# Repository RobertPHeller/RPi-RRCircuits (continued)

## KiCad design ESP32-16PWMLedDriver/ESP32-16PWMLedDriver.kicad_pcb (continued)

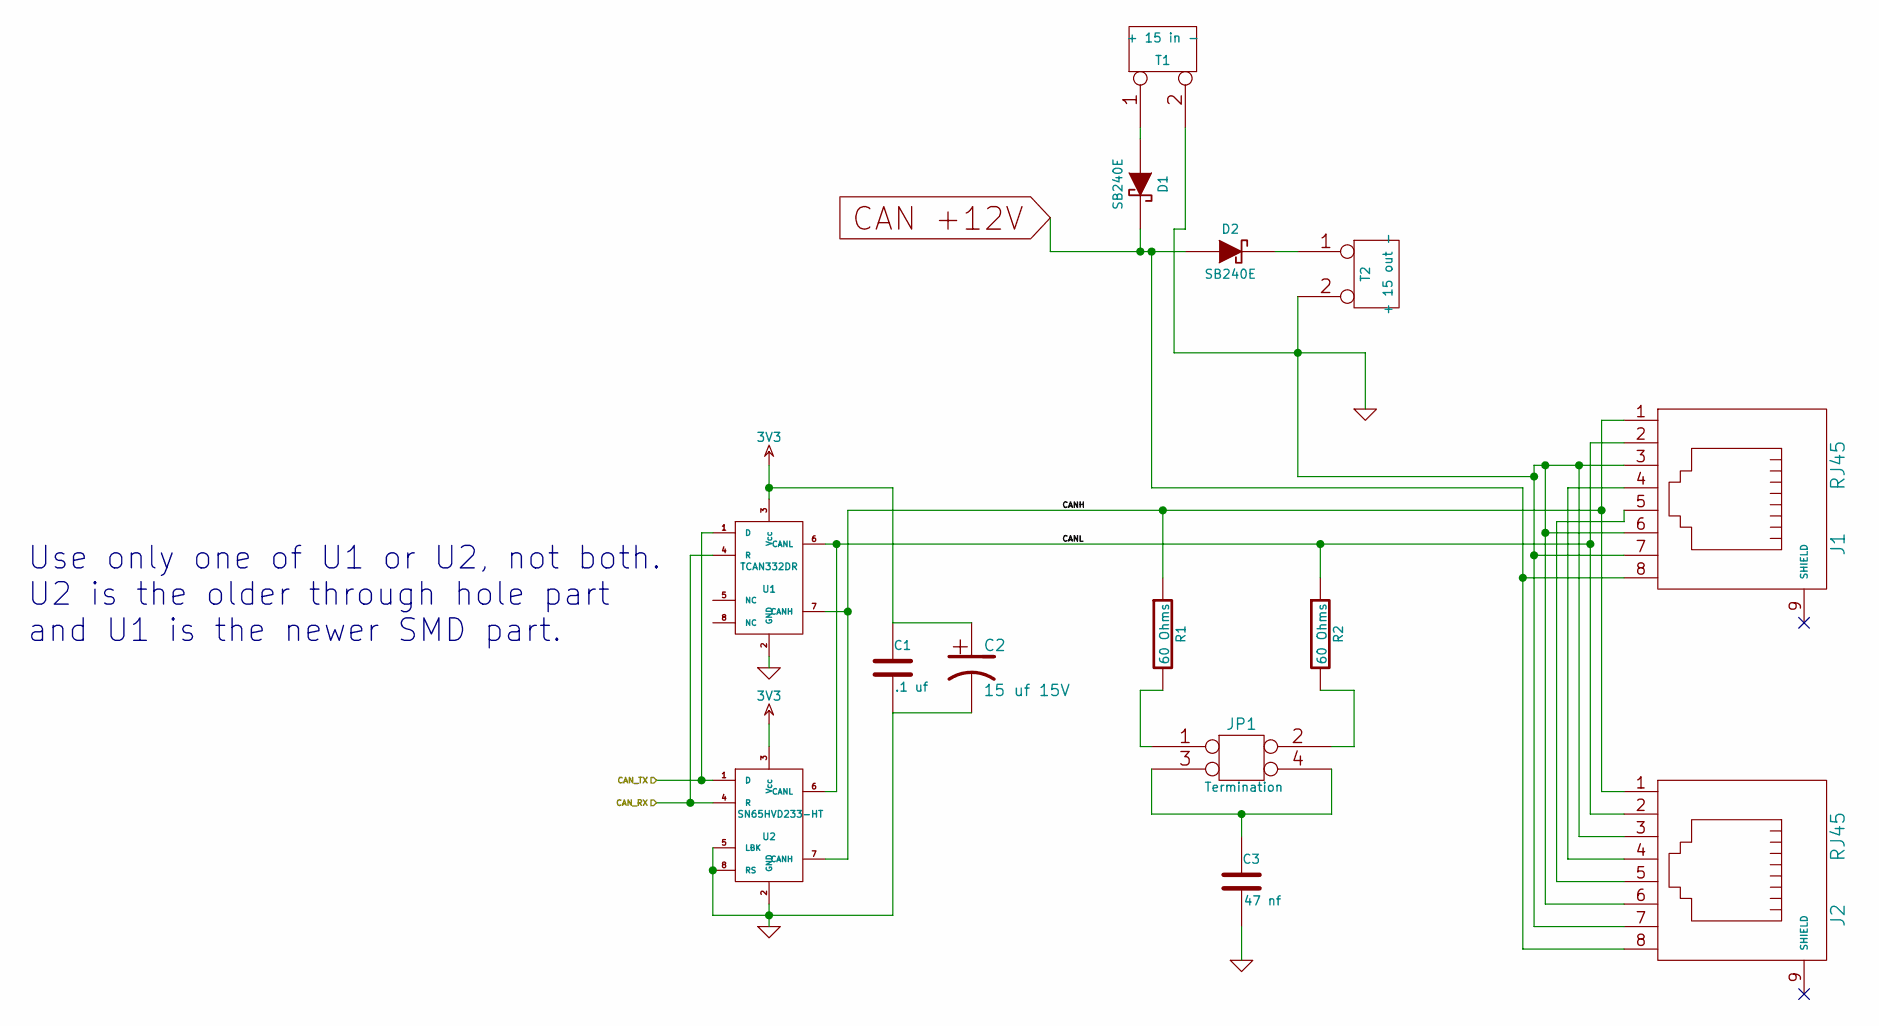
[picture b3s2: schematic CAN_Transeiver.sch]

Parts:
C1: .1 uf
C2: 15 uf 15V
C3: 47 nf
D1, D2: SB240E
J1, J2: RJ45
JP1: Termination
R1, R2: 60 Ohms
T1: + 15 in -
T2: + 15 out -
U1: TCAN332DR
U2: SN65HVD233-HT

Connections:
3V3: C1.1, C2.1, U1.3 (Vcc), U2.3 (Vcc); also elsewhere on the board
/CAN Transceiver/CANH: J1.1, J2.1, R1.1, U1.7 (CANH), U2.7 (CANH)
/CAN Transceiver/CANL: J1.2, J2.2, R2.1, U1.6 (CANL), U2.6 (CANL)
/CAN Transceiver/CAN_RX: U1.4 (R), U2.4 (R); also elsewhere on the board
/CAN Transceiver/CAN_TX: U1.1 (D), U2.1 (D); also elsewhere on the board
CAN +12V: D1.2 (K), D2.1 (A), J1.8, J2.8; also elsewhere on the board
GND: C1.2, C2.2, C3.2, J1.3, J1.6, J1.7, J2.3, J2.6, J2.7, T1.2 (PM), T2.2 (PM), U1.2 (GND), U2.2 (GND), U2.5 (LBK), U2.8 (RS); also elsewhere on the board
unnamed: J1.4, J2.4
unnamed: J1.5, J2.5
unnamed: D1.1 (A), T1.1
unnamed: D2.2 (K), T2.1
unnamed: JP1.2, R2.2
unnamed: C3.1, JP1.3, JP1.4
unnamed: JP1.1, R1.2

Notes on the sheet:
Use only one of U1 or U2, not both. U2 is the older through hole part and U1 is the newer SMD part.

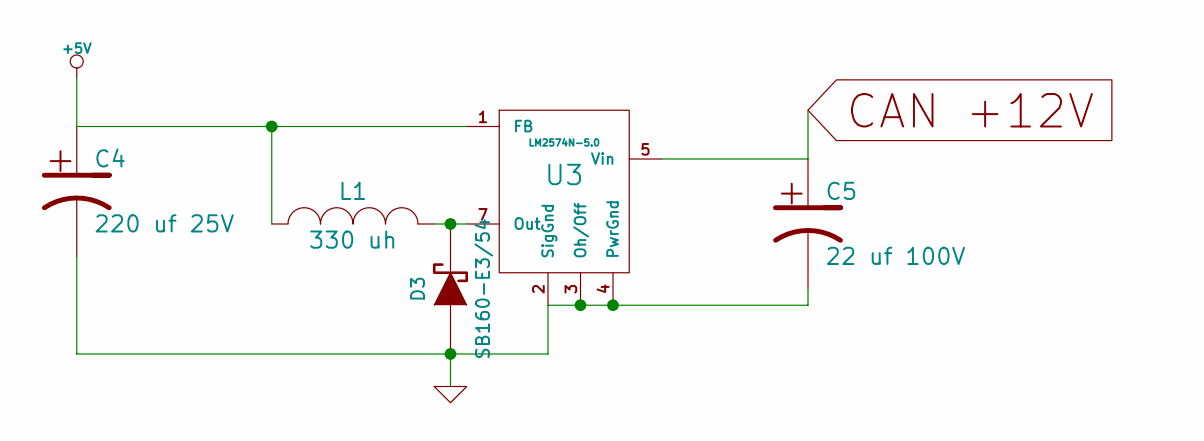
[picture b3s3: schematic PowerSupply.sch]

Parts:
C4: 220 uf 25V
C5: 22 uf 100V
D3: SB160-E3/54
L1: 330 uh
U3: LM2574N-5.0

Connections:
+5V: C4.1, L1.1, U3.1 (FB); also elsewhere on the board
CAN +12V: C5.1, U3.5 (Vin); also elsewhere on the board
GND: C4.2, C5.2, D3.1 (A), U3.2 (SigGnd), U3.3 (Oh/Off), U3.4 (PwrGnd); also elsewhere on the board
unnamed: D3.2 (K), L1.2, U3.7 (Out)

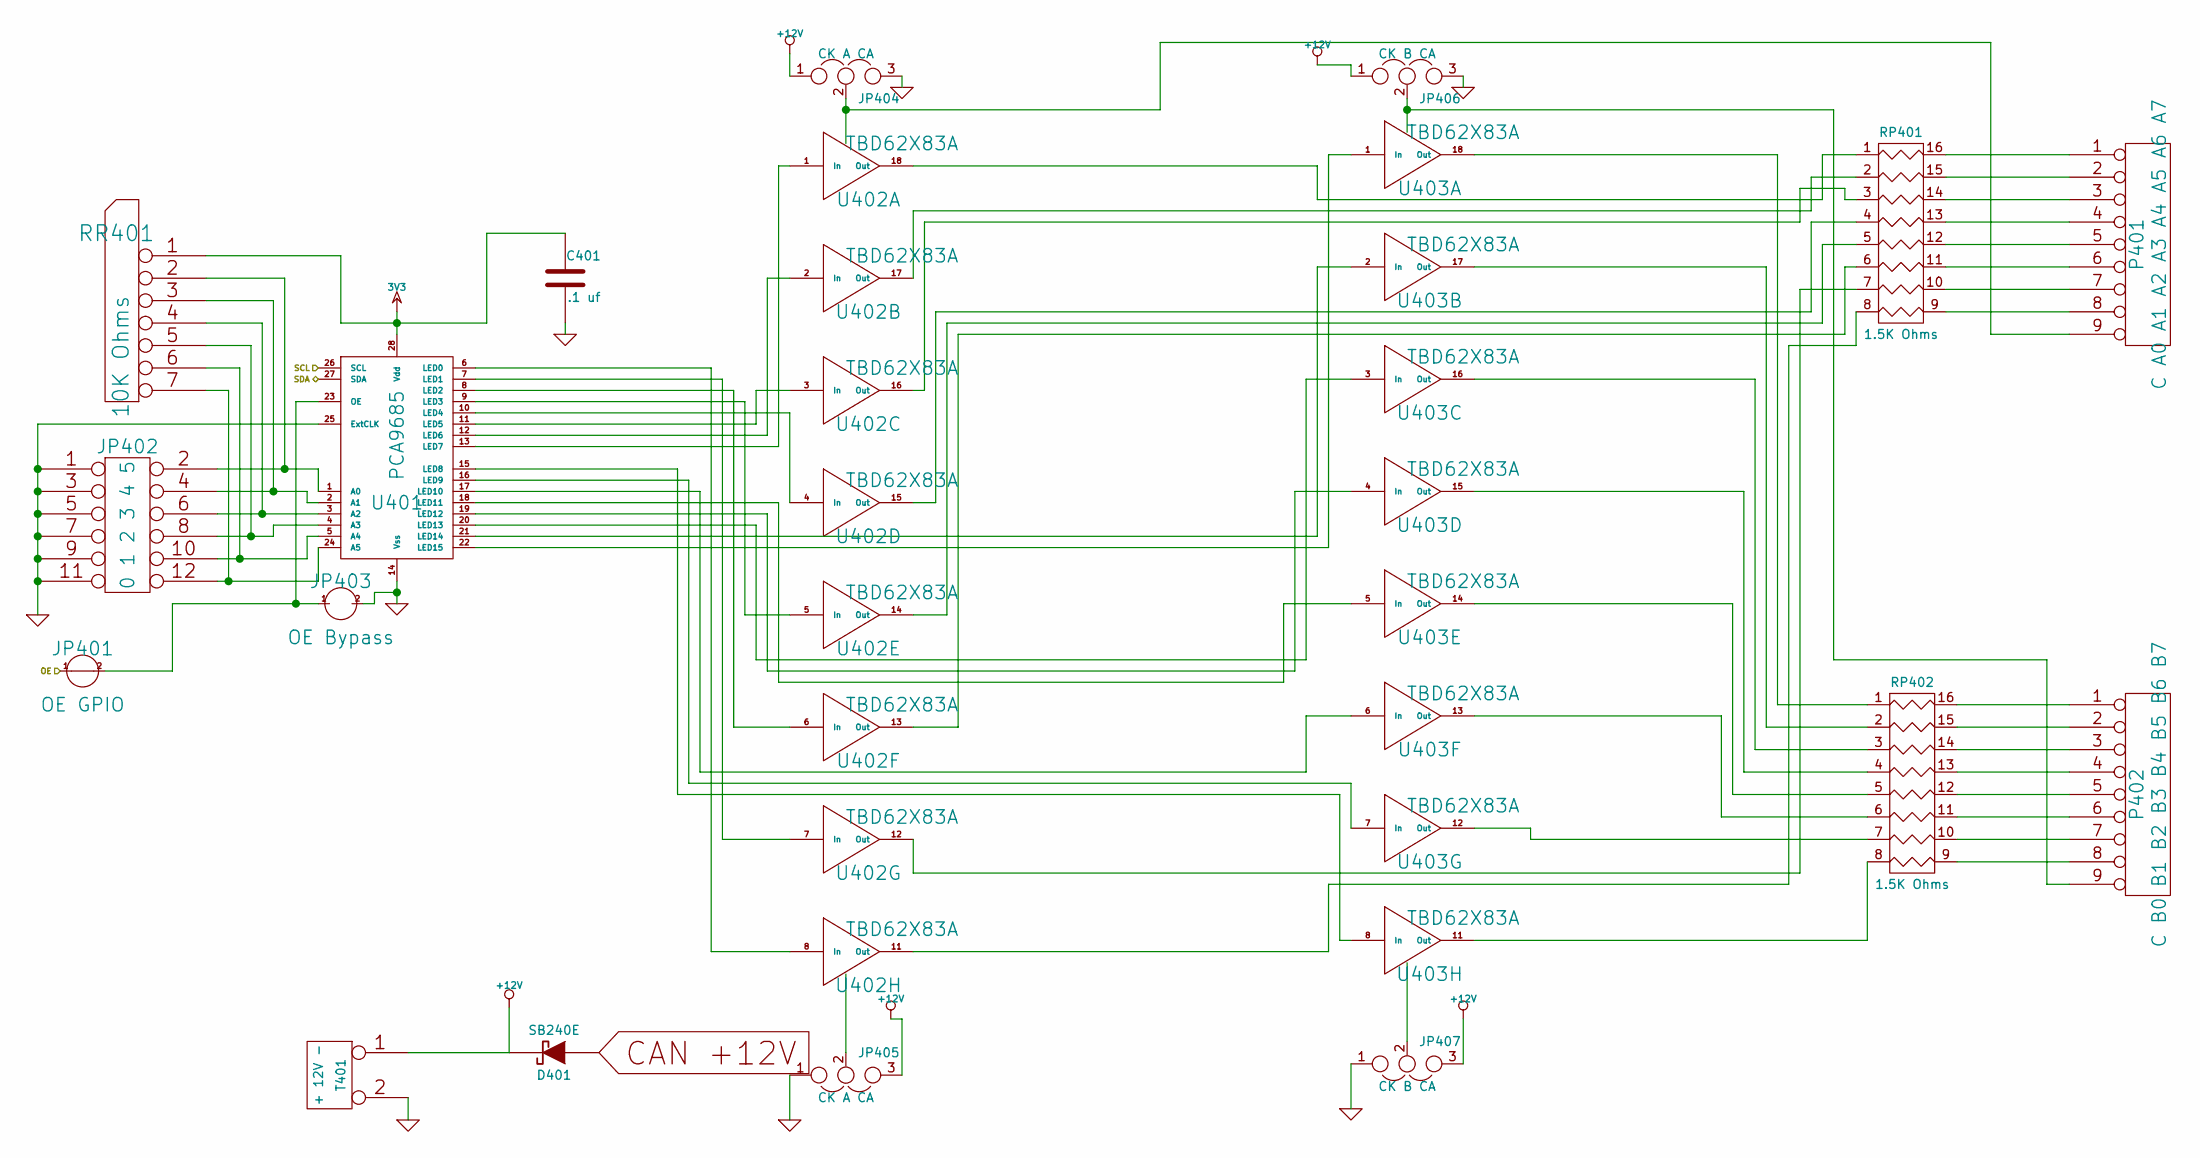
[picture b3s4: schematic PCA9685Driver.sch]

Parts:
C401: .1 uf
D401: SB240E
JP401: OE GPIO
JP402: 0 1 2 3 4 5
JP403: OE Bypass
JP404, JP405: CK A CA
JP406, JP407: CK B CA
P401: C A0 A1 A2 A3 A4 A5 A6 A7
P402: C B0 B1 B2 B3 B4 B5 B6 B7
RP401, RP402: 1.5K Ohms
RR401: 10K Ohms
T401: + 12V -
U401: PCA9685
U402, U403: TBD62X83A

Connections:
3V3: C401.1, RR401.1 (COM), U401.28 (Vdd); also elsewhere on the board
+12V: D401.2 (K), JP404.1, JP405.3, JP406.1, JP407.3, T401.1
/PCA9685 Driver/OE: JP401.1; also elsewhere on the board
/PCA9685 Driver/SCL: U401.26 (SCL); also elsewhere on the board
/PCA9685 Driver/SDA: U401.27 (SDA); also elsewhere on the board
CAN +12V: D401.1 (A); also elsewhere on the board
GND: C401.2, JP402.1, JP402.3, JP402.5, JP402.7, JP402.9, JP402.11, JP403.2, JP404.3, JP405.1, JP406.3, JP407.1, T401.2 (PM), U401.14 (Vss), U401.25 (ExtCLK); also elsewhere on the board
unnamed: P401.4, RP401.13 (R4)
unnamed: P401.5, RP401.12 (R5)
unnamed: P401.6, RP401.11 (R6)
unnamed: P401.7, RP401.10 (R7)
unnamed: P401.8, RP401.9 (R8)
unnamed: P402.1, RP402.16 (R1)
unnamed: P402.2, RP402.15 (R2)
unnamed: P402.3, RP402.14 (R3)
unnamed: P402.4, RP402.13 (R4)
unnamed: P402.5, RP402.12 (R5)
unnamed: P402.6, RP402.11 (R6)
unnamed: P402.7, RP402.10 (R7)
unnamed: P402.8, RP402.9 (R8)
unnamed: P401.3, RP401.14 (R3)
unnamed: P401.2, RP401.15 (R2)
unnamed: P401.1, RP401.16 (R1)
unnamed: JP406.2, P402.9, U403.10 (OC)
unnamed: JP404.2, P401.9, U402.10 (OC)
unnamed: RP401.5, U402.14 (Out)
unnamed: RP401.4, U402.15 (Out)
unnamed: RP401.3, U402.16 (Out)
unnamed: RP401.2, U402.17 (Out)
unnamed: RP401.1, U402.18 (Out)
unnamed: U401.19 (LED12), U403.4 (In)
unnamed: U401.20 (LED13), U403.3 (In)
unnamed: U401.21 (LED14), U403.2 (In)
unnamed: U401.22 (LED15), U403.1 (In)
unnamed: U401.6 (LED0), U402.8 (In)
unnamed: U401.8 (LED2), U402.6 (In)
unnamed: U401.9 (LED3), U402.5 (In)
unnamed: U401.10 (LED4), U402.4 (In)
unnamed: U401.11 (LED5), U402.3 (In)
unnamed: JP405.2, U402.9 (IC)
unnamed: JP407.2, U403.9 (IC)
unnamed: U401.15 (LED8), U403.8 (In)
unnamed: U401.16 (LED9), U403.7 (In)
unnamed: U401.7 (LED1), U402.7 (In)
unnamed: U401.17 (LED10), U403.6 (In)
unnamed: U401.18 (LED11), U403.5 (In)
unnamed: JP402.4, RR401.3, U401.2 (A1)
unnamed: JP402.6, RR401.4, U401.3 (A2)
unnamed: JP402.8, RR401.5, U401.4 (A3)
unnamed: JP402.10, RR401.6, U401.5 (A4)
unnamed: JP401.2, JP403.1, U401.23 (OE)
unnamed: RP402.5, U403.14 (Out)
unnamed: RP402.4, U403.15 (Out)
unnamed: RP402.3, U403.16 (Out)
unnamed: RP402.2, U403.17 (Out)
unnamed: RP402.1, U403.18 (Out)
unnamed: RP401.8, U402.11 (Out)
unnamed: RP401.7, U402.12 (Out)
unnamed: RP401.6, U402.13 (Out)
unnamed: JP402.12, RR401.7, U401.24 (A5)
unnamed: JP402.2, RR401.2, U401.1 (A0)
unnamed: RP402.8, U403.11 (Out)
unnamed: RP402.7, U403.12 (Out)
unnamed: RP402.6, U403.13 (Out)
unnamed: U401.12 (LED6), U402.2 (In)
unnamed: U401.13 (LED7), U402.1 (In)

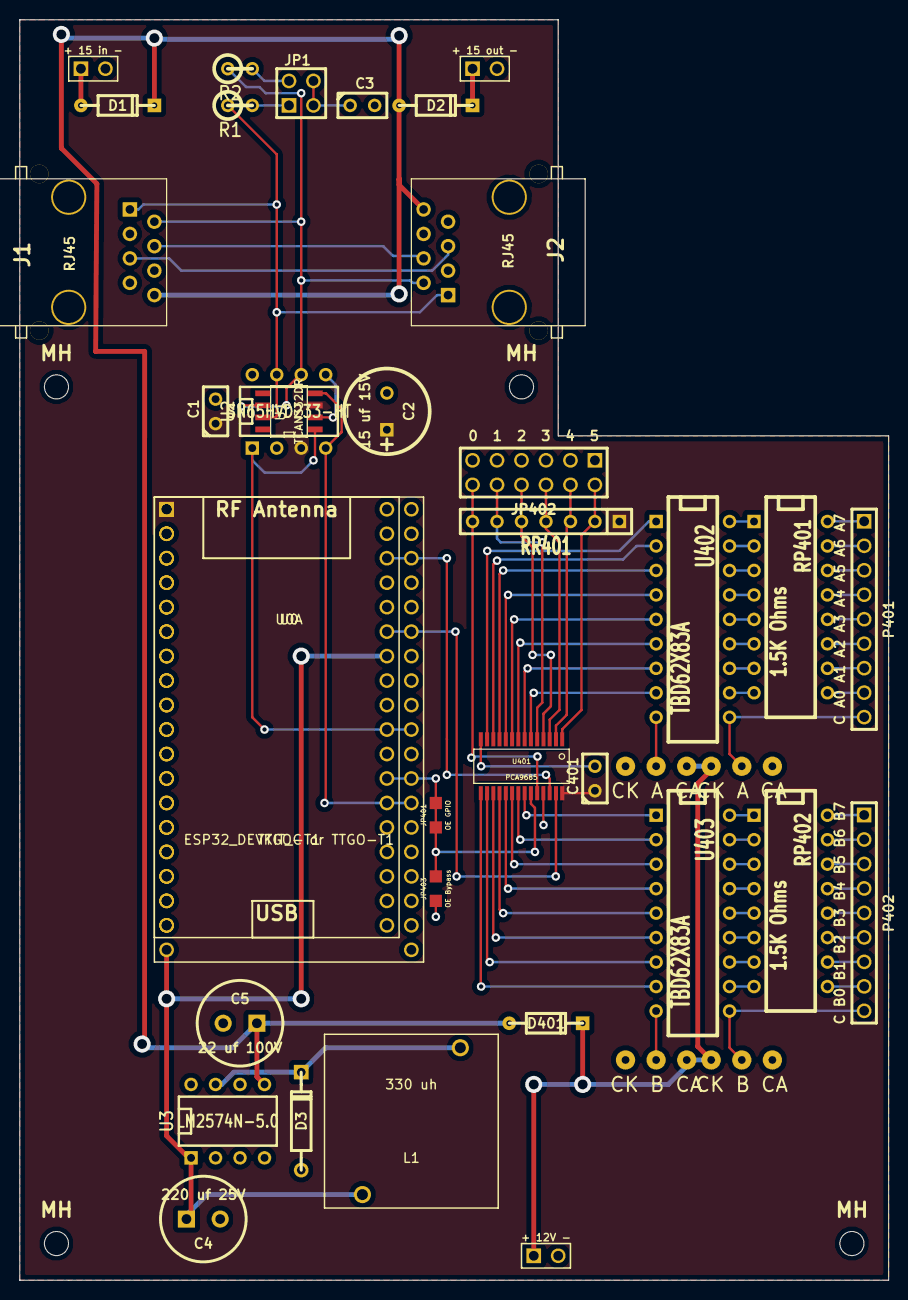
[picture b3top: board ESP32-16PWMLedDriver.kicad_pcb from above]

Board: 2 copper layers, 90.2 x 130.8 mm, 43 parts (0 on the bottom side), 79 nets.

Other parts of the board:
MH: MountingHole_2-5mm_RevA_Date21Jun2010
MH#2, MH#3, MH#4: MountingHole_2-5mm_RevA_Date21Jun2010
U0A: TTGO-T1; TIGO-T1

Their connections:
3V3: U0A.1; also elsewhere on the board
+5V: U0A.30; also elsewhere on the board
/CAN Transceiver/CAN_RX: U0A.24; also elsewhere on the board
/CAN Transceiver/CAN_TX: U0A.27; also elsewhere on the board
/PCA9685 Driver/OE: U0A.25; also elsewhere on the board
/PCA9685 Driver/SCL: U0A.34; also elsewhere on the board
/PCA9685 Driver/SDA: U0A.31; also elsewhere on the board
GND: U0A.14, U0A.36; also elsewhere on the board

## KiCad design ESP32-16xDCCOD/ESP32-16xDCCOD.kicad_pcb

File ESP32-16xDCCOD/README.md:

# ESP32-16xDCCOD

Backplane for up to 16 DCCOD_SMD's using a ESP32 MCU.  Meant as a thought 
experiment to see what this would cost, etc.

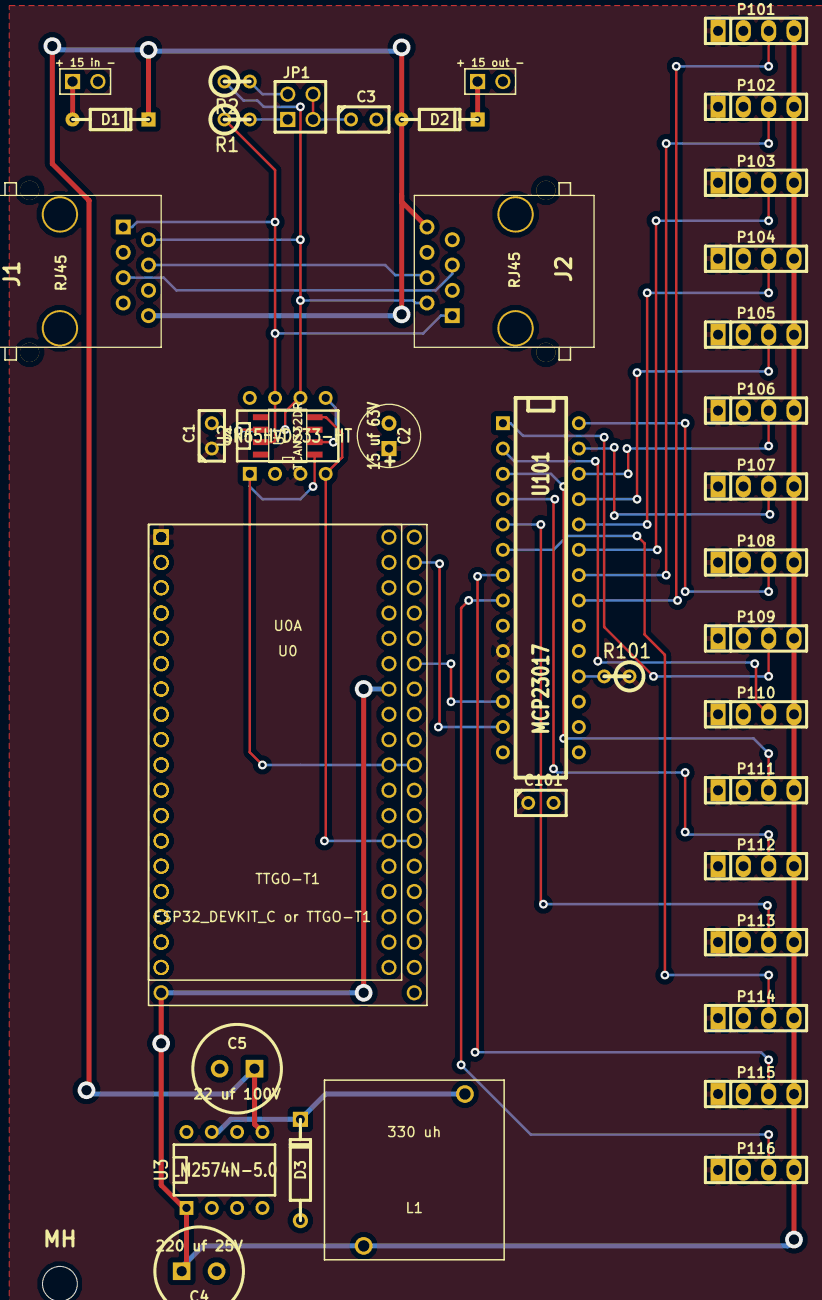
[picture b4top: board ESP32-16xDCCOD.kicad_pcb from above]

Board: 2 copper layers, 43 parts (0 on the bottom side), 35 nets.

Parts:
C1, C101: .1 uf; C1
C2: 15 uf 63V; C1V7
C3: 47 nf; C1
C4: 220 uf 25V; C1-3V8
C5: 22 uf 100V; C1-3V8
D1, D2: SB240E; DO-35
D3: SB160-E3/54; DO-41
J1, J2: RJ45; RJ45_8N-S
JP1: Termination; PIN_ARRAY_2X2
L1: 330 uh; PE-LowProfile
MH: MountingHole_3-5mm_RevA_Date21Jun2010
MH#2, MH#3: MountingHole_3-5mm_RevA_Date21Jun2010
P101, P102, P103, P104, P105, P106, P107, P108, P109, P110, P111, P112, P113, P114, P115, P116: CONN_4; pin_socket_4
R1, R2: 60 Ohms; R1
R101: 10K Ohms; R1
T1: + 15 in -; ScrewTerm2.54-2
T2: + 15 out -; ScrewTerm2.54-2
U0: ESP32_DEVKIT_C or TTGO-T1; ESP32-Devkit-C
U0A: TTGO-T1; TIGO-T1
U1: TCAN332DR; SOIC-8_N
U2: SN65HVD233-HT; DIP-8__300
U3: LM2574N-5.0; DIP-8__300
U101: MCP23017; DIP-28__300

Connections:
3V3: C1.1, C2.1, C101.1, P101.1, P102.1, P103.1, P104.1, P105.1, P106.1, P107.1, P108.1, P109.1, P110.1, P111.1, P112.1, P113.1, P114.1, P115.1, P116.1, R101.1, U0.1, U0A.1, U1.3, U2.3, U101.10
+5V: C4.1, L1.1, P101.4, P102.4, P103.4, P104.4, P105.4, P106.4, P107.4, P108.4, P109.4, P110.4, P111.4, P112.4, P113.4, P114.4, P115.4, P116.4, U0.19, U0A.30, U3.1
+12V: C5.1, D1.2, D2.1, J1.8, J2.8, U3.5
/CAN Transceiver/CANH: J1.1, J2.1, R1.1, U1.7, U2.7
/CAN Transceiver/CANL: J1.2, J2.2, R2.1, U1.6, U2.6
/CAN Transceiver/CAN_RX: U0.26, U0A.24, U1.4, U2.4
/CAN Transceiver/CAN_TX: U0.29, U0A.27, U1.1, U2.1
/OD1: P101.3, U101.21
/OD2: P102.3, U101.22
/OD3: P103.3, U101.23
/OD4: P104.3, U101.24
/OD5: P105.3, U101.25
/OD6: P106.3, U101.26
/OD7: P107.3, U101.27
/OD8: P108.3, U101.28
/OD9: P109.3, U101.1
/OD10: P110.3, U101.2
/OD11: P111.3, U101.3
/OD12: P112.3, U101.4
/OD13: P113.3, U101.5
/OD14: P114.3, U101.6
/OD15: P115.3, U101.7
/OD16: P116.3, U101.8
/SCL: U0.33, U101.12
/SDA: U0.37, U101.13
GND: C1.2, C2.2, C3.2, C4.2, C5.2, C101.2, D3.1, J1.3, J1.6, J1.7, J2.3, J2.6, J2.7, P101.2, P102.2, P103.2, P104.2, P105.2, P106.2, P107.2, P108.2, P109.2, P110.2, P111.2, P112.2, P113.2, P114.2, P115.2, P116.2, T1.2, T2.2, U0.14, U0.38, U0A.14, U0A.36, U1.2, U2.2, U2.5, U2.8, U3.2, U3.3, U3.4, U101.9, U101.15, U101.16, U101.17
unnamed: R101.2, U101.18
unnamed: J1.4, J2.4
unnamed: J1.5, J2.5
unnamed: D1.1, T1.1
unnamed: D2.2, T2.1
unnamed: JP1.2, R2.2
unnamed: C3.1, JP1.3, JP1.4
unnamed: JP1.1, R1.2
unnamed: D3.2, L1.2, U3.7

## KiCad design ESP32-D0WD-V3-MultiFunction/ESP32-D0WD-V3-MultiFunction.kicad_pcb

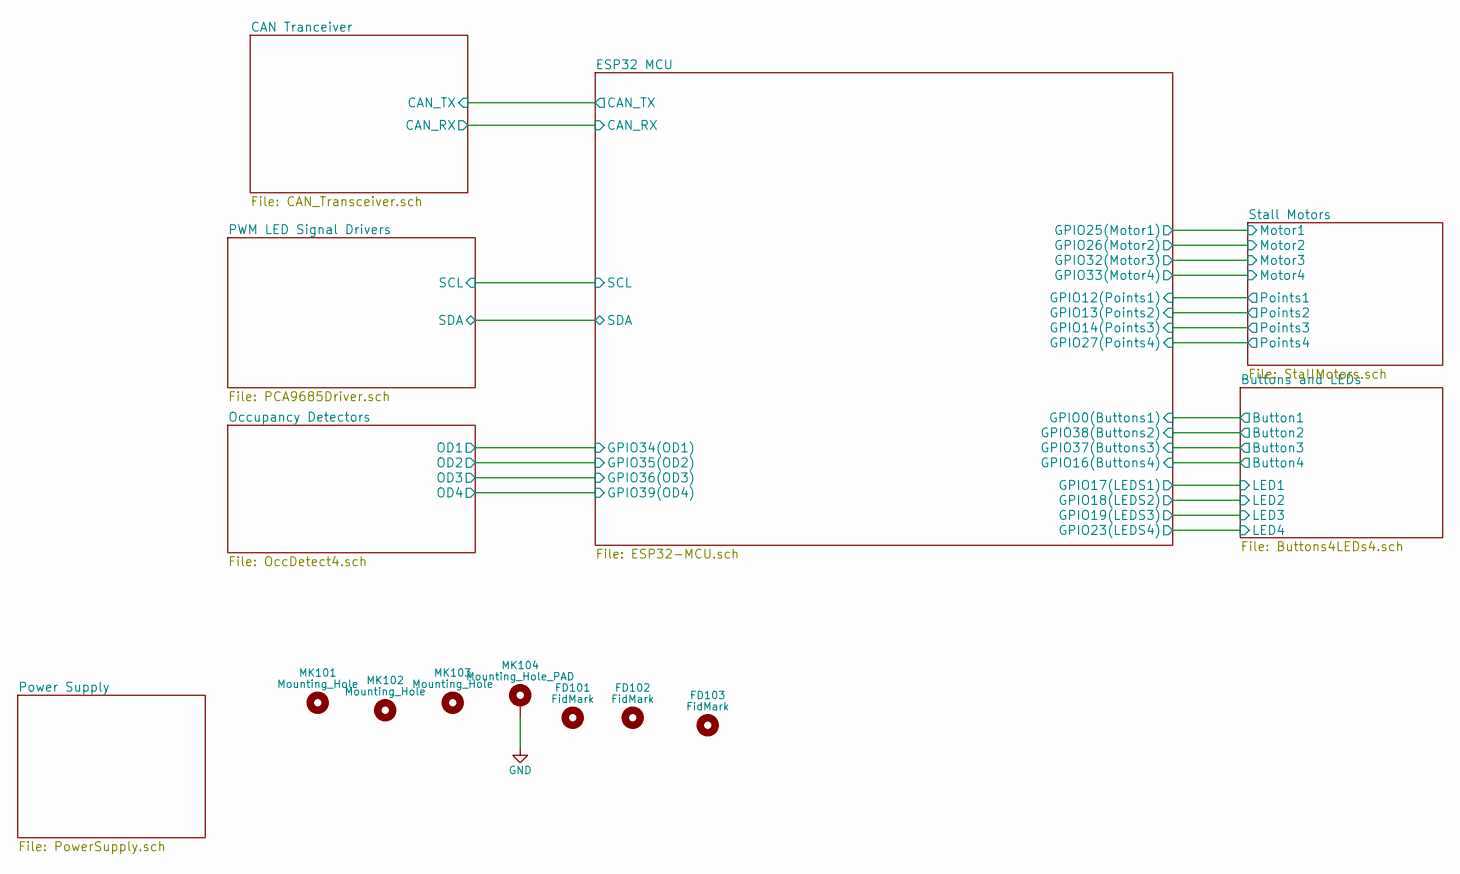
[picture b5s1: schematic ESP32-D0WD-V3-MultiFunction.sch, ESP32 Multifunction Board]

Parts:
FD101, FD102, FD103: FidMark; Fiducial_1mm_Dia_2.54mm_Outer_CopperTop
MK101, MK102, MK103: Mounting_Hole; MountingHole_3.7mm
MK104: Mounting_Hole_PAD; MountingHole_3.7mm_Pad

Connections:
GND: MK104.1; also elsewhere on the board

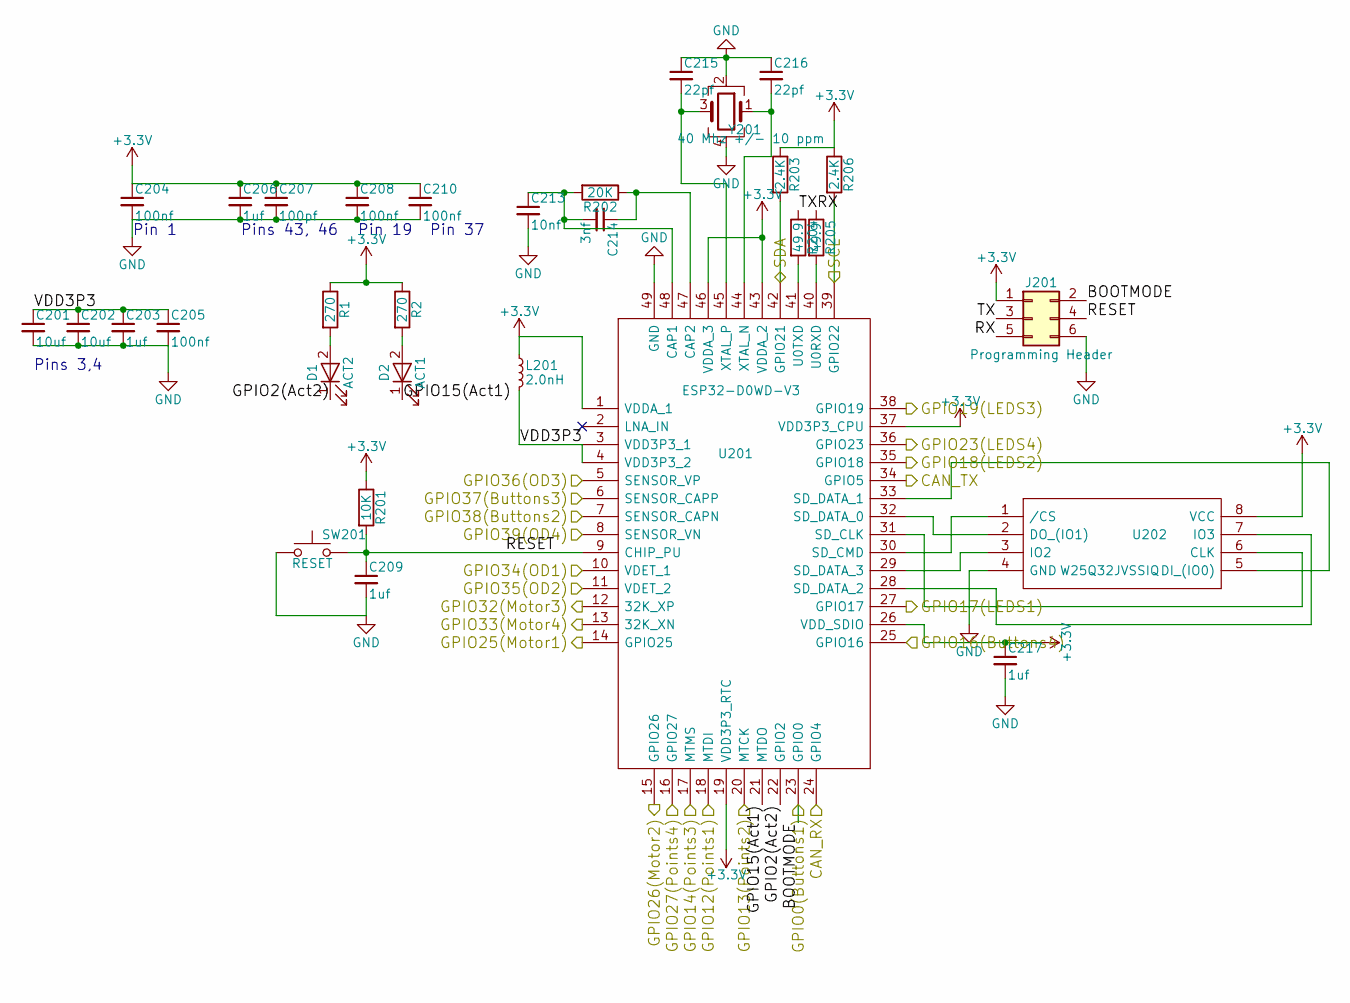
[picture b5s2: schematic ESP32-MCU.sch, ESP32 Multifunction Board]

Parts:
C201, C202: 10uf; C_0805; Mouser Part Number 187-CL21A106MQFNNNE
C203, C206, C209, C217: 1uf; C_0402; Mouser Part Number 80-C0402C101K8RAUTO
C204, C205, C208, C210: 100nf; C_0402; Mouser Part Number 710-885012105001
C207: 100pf; C_0402; Mouser Part Number 80-C0402C101K3RAUTO
C213: 10nf; C_0402; Mouser Part Number 81-GRM155R61E103KA1D
C214: 3nf; C_0402; Mouser Part Number 81-GRM1557U1A302JA1D
C215, C216: 22pf; C_0402; Mouser Part Number 187-CL05C220JB5NNND
D1: ACT2; LED_0402; Mouser Part Number 710-150040SS73220
D2: ACT1; LED_0402; Mouser Part Number 710-150040GS73220
J201: Programming Header; Pin_Header_Straight_2x03_Pitch2.54mm; Mouser Part Number 523-G800LQ593032HR
L201: 2.0nH; L_0402; Mouser Part Number 810-MLG1005S2N0ST000
R1, R2: 270; R_0402; Mouser Part Number 754-RR0510P-271D
R201: 10K; R_0402; Mouser Part Number 603-RC0402JR-1310KL
R202: 20K; R_0402; Mouser Part Number 791-RMC10K203FTH
R203, R206: 2.4K; R_0402; Mouser Part Number 71-CRCW06032K40JNEAC
R204, R205: 49.9; R_0402; Mouser Part Number 791-RMC1/16SK49R9FTH
SW201: RESET; PTS647SM38SMTR2LFS; Mouser Part Number 611-PTS647SN70SMTR2L
U201: ESP32-D0WD-V3; QFN35P500X500X90-49N-D; Manufacturer_Part_Number ESP32-D0WD-V3; Mouser Part Number 356-ESP32-D0WD-V3
U202: W25Q32JVSSIQ; SOIC-8_3.9x4.9mm_Pitch1.27mm; Mouser Part Number 454-W25Q32JVSSIQ
Y201: 40 Mhz +/- 10 ppm; FA20_H; Mouser Part Number 732-FA-20H40MF10Z-W3

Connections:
/Buttons and LEDs/Button1: J201.2, U201.23 (GPIO0); also elsewhere on the board
/Buttons and LEDs/Button2: U201.7 (SENSOR_CAPN); also elsewhere on the board
/Buttons and LEDs/Button3: U201.6 (SENSOR_CAPP); also elsewhere on the board
/Buttons and LEDs/Button4: U201.25 (GPIO16); also elsewhere on the board
/CAN Tranceiver/CAN_RX: U201.24 (GPIO4); also elsewhere on the board
/CAN Tranceiver/CAN_TX: U201.34 (GPIO5); also elsewhere on the board
/ESP32 MCU/GPIO2(Act2): D1.1 (K), U201.22 (GPIO2)
/ESP32 MCU/GPIO12(Points1): U201.18 (MTDI); also elsewhere on the board
/ESP32 MCU/GPIO13(Points2): U201.20 (MTCK); also elsewhere on the board
/ESP32 MCU/GPIO14(Points3): U201.17 (MTMS); also elsewhere on the board
/ESP32 MCU/GPIO15(Act1): D2.1 (K), U201.21 (MTDO)
/ESP32 MCU/GPIO17(LEDS1): U201.27 (GPIO17); also elsewhere on the board
/ESP32 MCU/GPIO18(LEDS2): U201.35 (GPIO18); also elsewhere on the board
/ESP32 MCU/GPIO19(LEDS3): U201.38 (GPIO19); also elsewhere on the board
/ESP32 MCU/GPIO23(LEDS4): U201.36 (GPIO23); also elsewhere on the board
/ESP32 MCU/GPIO25(Motor1): U201.14 (GPIO25); also elsewhere on the board
/ESP32 MCU/GPIO26(Motor2): U201.15 (GPIO26); also elsewhere on the board
/ESP32 MCU/GPIO27(Points4): U201.16 (GPIO27); also elsewhere on the board
/ESP32 MCU/GPIO32(Motor3): U201.12 (32K_XP); also elsewhere on the board
/ESP32 MCU/GPIO33(Motor4): U201.13 (32K_XN); also elsewhere on the board
/ESP32 MCU/GPIO34(OD1): U201.10 (VDET_1); also elsewhere on the board
/ESP32 MCU/GPIO35(OD2): U201.11 (VDET_2); also elsewhere on the board
/ESP32 MCU/GPIO36(OD3): U201.5 (SENSOR_VP); also elsewhere on the board
/ESP32 MCU/GPIO39(OD4): U201.8 (SENSOR_VN); also elsewhere on the board
/ESP32 MCU/RESET: C209.1, J201.4, R201.2, SW201.2, U201.9 (CHIP_PU)
/ESP32 MCU/RX: J201.5, R205.1
/ESP32 MCU/SCL: R206.2, U201.39 (GPIO22); also elsewhere on the board
/ESP32 MCU/SDA: R203.2, U201.42 (GPIO21); also elsewhere on the board
/ESP32 MCU/TX: J201.3, R204.1
/ESP32 MCU/VDD3P3: C201.1, C202.1, C203.1, C205.1, L201.2, U201.3 (VDD3P3_1), U201.4 (VDD3P3_2)
GND: C201.2, C202.2, C203.2, C204.2, C205.2, C206.2, C207.2, C208.2, C209.2, C210.2, C213.2, C215.1, C216.1, C217.2, J201.6, SW201.1, U201.49 (GND), U202.4 (GND), Y201.2, Y201.4; also elsewhere on the board
unnamed: C213.1, C214.2, R202.2, U201.48 (CAP1)
unnamed: C214.1, R202.1, U201.47 (CAP2)
unnamed: C215.2, U201.45 (XTAL_P), Y201.3
unnamed: C216.2, U201.44 (XTAL_N), Y201.1
unnamed: D1.2 (A), R1.2
unnamed: D2.2 (A), R2.2
unnamed: R204.2, U201.41 (U0TXD)
unnamed: R205.2, U201.40 (U0RXD)
unnamed: U201.28 (SD_DATA_2), U202.7 (IO3)
unnamed: U201.29 (SD_DATA_3), U202.3 (IO2)
unnamed: U201.30 (SD_CMD), U202.1 (/CS)
unnamed: U201.31 (SD_CLK), U202.6 (CLK)
unnamed: U201.32 (SD_DATA_0), U202.2 (DO_(IO1))
unnamed: U201.33 (SD_DATA_1), U202.5 (DI_(IO0))

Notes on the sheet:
Pins 3,4
Pin 1
Pins 43, 46
Pin 19
Pin 37

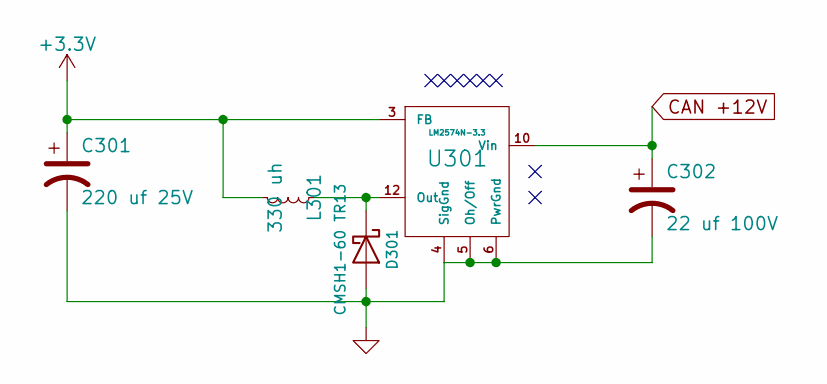
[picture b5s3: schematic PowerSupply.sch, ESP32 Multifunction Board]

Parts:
C301: 220 uf 25V; CP_Elec_8x10; Mouser Part Number 647-UWT1E221MNL1GS
C302: 22 uf 100V; CP_Elec_8x10; Mouser Part Number 647-UUX2A220MNL6GS
D301: CMSH1-60 TR13; D_SMB; Mouser Part Number 610-CMSH1-60TR13
L301: 330 uh; SRN1060; Mouser Part Number 652-SRN1060-331M
U301: LM2574N-3.3; SOIC-14_7.4x8.7mm_Pitch1.27mm; Mouser Part Number 926-LM2574MX33NOPB

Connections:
CAN +12V: C302.1, U301.10 (Vin); also elsewhere on the board
GND: C301.2, C302.2, D301.2 (A), U301.4 (SigGnd), U301.5 (Oh/Off), U301.6 (PwrGnd); also elsewhere on the board
unnamed: D301.1 (K), L301.1, U301.12 (Out)

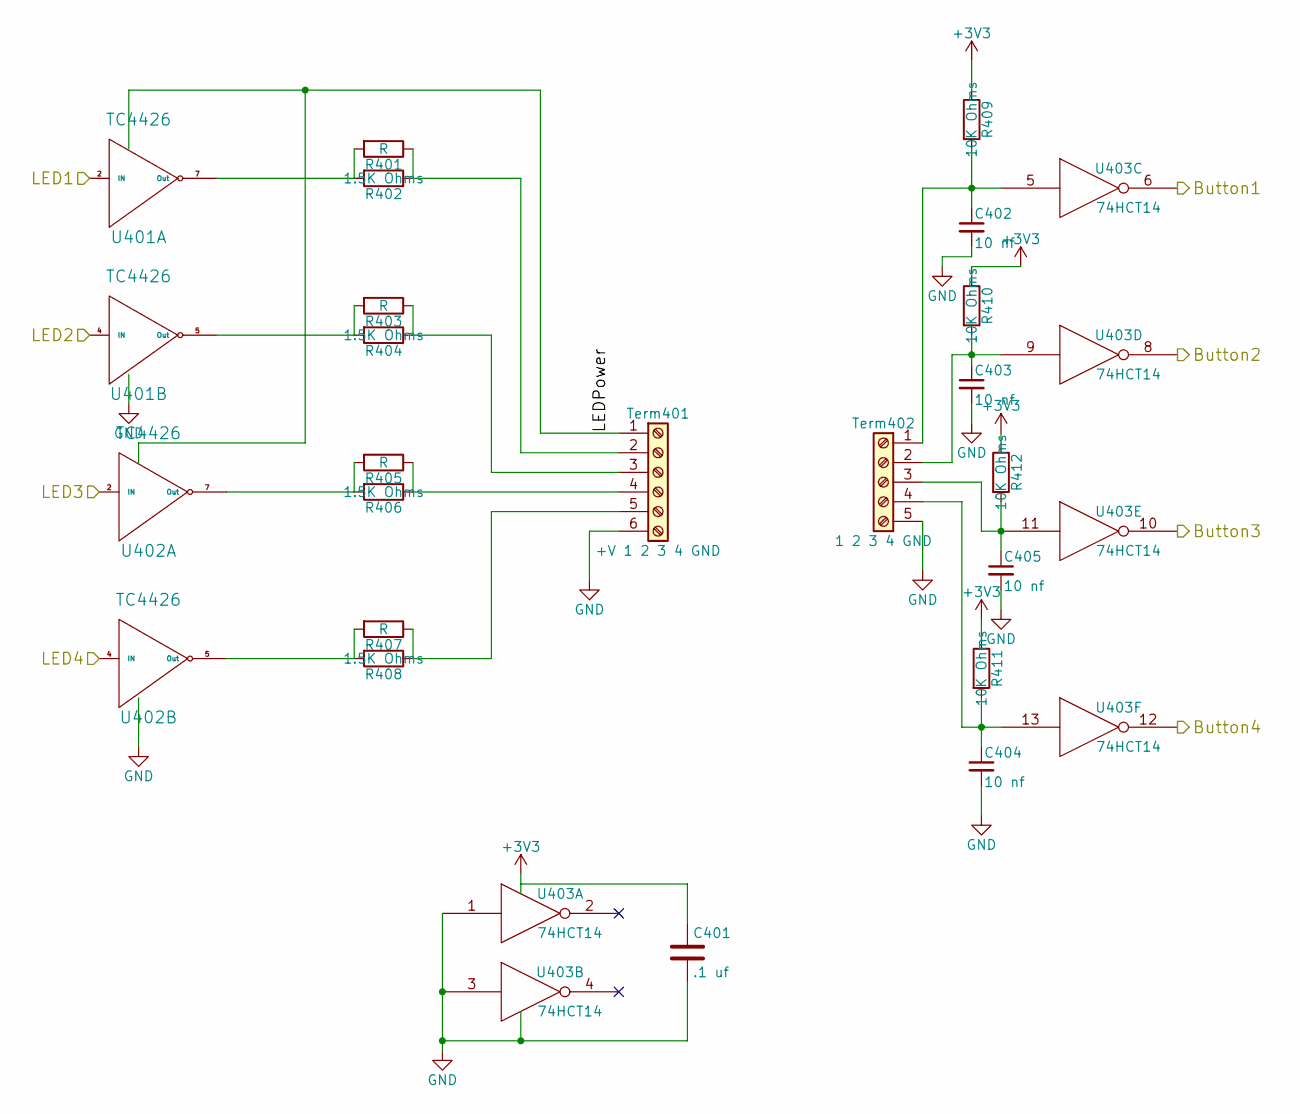
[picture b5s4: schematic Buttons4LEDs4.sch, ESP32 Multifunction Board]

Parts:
C401: .1 uf; C_0603
C402, C403, C404, C405: 10 nf; C_0603; Mouser Part Number 710-885382206002
R401, R403, R405, R407: R; R_Axial_DIN0207_L6.3mm_D2.5mm_P7.62mm_Horizontal
R402, R404, R406, R408: 1.5K Ohms; R_0603; Mouser Part Number 71-CRCW06031K50JNEAC
R409, R410, R411, R412: 10K Ohms; R_0603; Mouser Part Number 71-CRCW060310K0JNEBC
Term401: +V 1 2 3 4 GND; TerminalBlock_Pheonix_MPT-2.54mm_6pol; Mouser Part Number 651-1725698
Term402: 1 2 3 4 GND; TerminalBlock_Pheonix_MPT-2.54mm_5pol; Mouser Part Number 651-1725685
U401, U402: TC4426; SOIC-8_3.9x4.9mm_Pitch1.27mm; Mouser Part Number 579-TC1426COA713
U403: 74HCT14; SOIC-14_3.9x8.7mm_Pitch1.27mm; Mouser Part Number 595-CD74HC14M

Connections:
/Buttons and LEDs/Button1: U403.6; also elsewhere on the board
/Buttons and LEDs/Button2: U403.8; also elsewhere on the board
/Buttons and LEDs/Button3: U403.10; also elsewhere on the board
/Buttons and LEDs/Button4: U403.12; also elsewhere on the board
/ESP32 MCU/GPIO17(LEDS1): U401.2 (IN); also elsewhere on the board
/ESP32 MCU/GPIO18(LEDS2): U401.4 (IN); also elsewhere on the board
/ESP32 MCU/GPIO19(LEDS3): U402.2 (IN); also elsewhere on the board
/ESP32 MCU/GPIO23(LEDS4): U402.4 (IN); also elsewhere on the board
GND: C401.2, C402.2, C403.2, C404.2, C405.2, Term401.6, Term402.5, U401.3 (GND), U402.3 (GND), U403.1, U403.3, U403.7 (GND); also elsewhere on the board
unnamed: C402.1, R409.2, Term402.1, U403.5
unnamed: C403.1, R410.2, Term402.2, U403.9
unnamed: C404.1, R411.2, Term402.4, U403.13
unnamed: C405.1, R412.2, Term402.3, U403.11
unnamed: R401.1, R402.1, Term401.2
unnamed: R401.2, R402.2, U401.7 (Out)
unnamed: R403.1, R404.1, Term401.3
unnamed: R403.2, R404.2, U401.5 (Out)
unnamed: R405.1, R406.1, Term401.4
unnamed: R405.2, R406.2, U402.7 (Out)
unnamed: R407.1, R408.1, Term401.5
unnamed: R407.2, R408.2, U402.5 (Out)
V+: Term401.1, U401.6 (V+), U402.6 (V+)
